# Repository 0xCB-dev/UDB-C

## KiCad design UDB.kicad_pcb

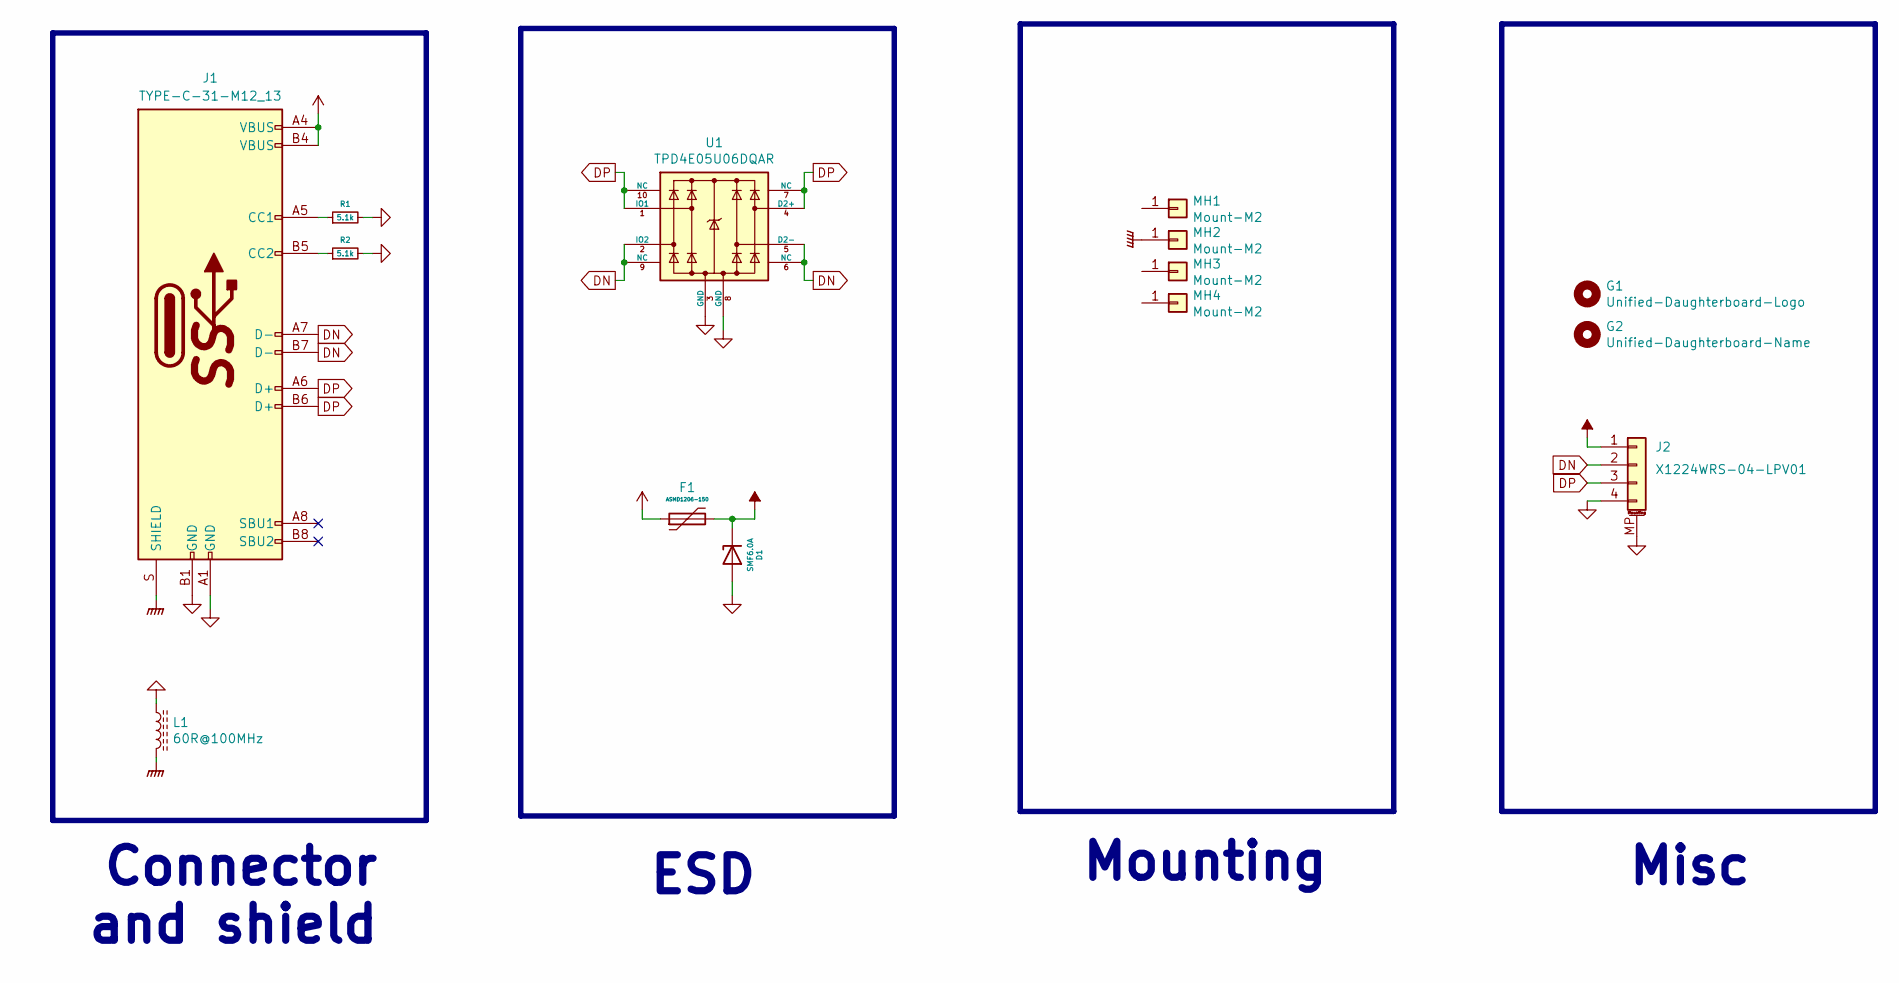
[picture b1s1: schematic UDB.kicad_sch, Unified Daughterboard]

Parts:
D1: SMF6.0A; D_SOD-123; Manufacturer Part Number SMF6.0A; LCSC C708002
F1: ASMD1206-150; Fuse_1206_3216Metric; Manufacturer Part Number ASMD1206-150; LCSC C135342
G1: Unified-Daughterboard-Logo; Unified-Daughterboard-Logo.pretty
G2: Unified-Daughterboard-Name; Unified-Daughterboard-Name.pretty
J1: TYPE-C-31-M12_13; TYPE-C-31-M-12; Manufacturer Part Number TYPE-C-31-M-12; LCSC C165948
J2: X1224WRS-04-LPV01; MOLEX_781710004_MountingReliefs; Manufacturer Part Number X1224WRS-04-LPV01; LCSC C528030
L1: 60R@100MHz; L_1206_3216Metric; Manufacturer Part Number MLB3216-600P4A(f); LCSC C33600
MH1, MH2, MH3, MH4: Mount-M2; Generic-Mounthole
R1, R2: 5.1k; R_0402_1005Metric; LCSC C138073
U1: TPD4E05U06DQAR; USON-10_2.5x1.0mm_P0.5mm; Manufacturer Part Number TPD4E05U06DQAR; LCSC C138714

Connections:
DN: J1.A7 (D-), J1.B7 (D-), J2.2, U1.2 (IO2), U1.5 (D2-), U1.6 (NC), U1.9 (NC)
DP: J1.A6 (D+), J1.B6 (D+), J2.3, U1.1 (IO1), U1.4 (D2+), U1.7 (NC), U1.10 (NC)
GND: D1.2 (A), J1.A1 (GND), J1.B1 (GND), J2.4, J2.MP (MountPin), L1.1, R1.2, R2.2, U1.3 (GND), U1.8 (GND)
GNDPWR: J1.S (SHIELD), L1.2, MH2.1
unnamed: J1.A5 (CC1), R1.1
unnamed: J1.B5 (CC2), R2.1
VBUS: F1.1, J1.A4 (VBUS), J1.B4 (VBUS)
VCOM: D1.1 (K), F1.2, J2.1

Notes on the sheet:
Connector and shield
Misc
Mounting
ESD

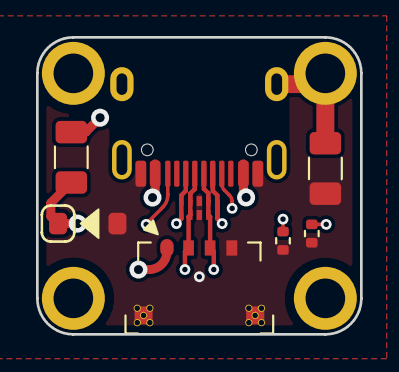
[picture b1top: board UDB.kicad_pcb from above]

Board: 4 copper layers, 18.0 x 16.5 mm, 13 parts (1 on the bottom side), 8 nets.

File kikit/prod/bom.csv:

Comment,Designator,Footprint,LCSC
SMF6.0A,D1,acheron_Components:D_SOD-123,C708002
ASMD1206-150,F1,Fuse:Fuse_1206_3216Metric,C135342
TYPE-C-31-M12_13,J1,acheron_Connectors:TYPE-C-31-M-12,C165948
X1224WRS-04-LPV01,J2,acheron_Connectors:MOLEX_781710004_MountingReliefs,C528030
60R@100MHz,L1,Inductor_SMD:L_1206_3216Metric,C33600
5.1k,"R1,R2",Resistor_SMD:R_0402_1005Metric,C138073
TPD4E05U06DQAR,U1,acheron_Components:USON-10_2.5x1.0mm_P0.5mm,C138714

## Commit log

2023-02-11 added kikit panel assembly
